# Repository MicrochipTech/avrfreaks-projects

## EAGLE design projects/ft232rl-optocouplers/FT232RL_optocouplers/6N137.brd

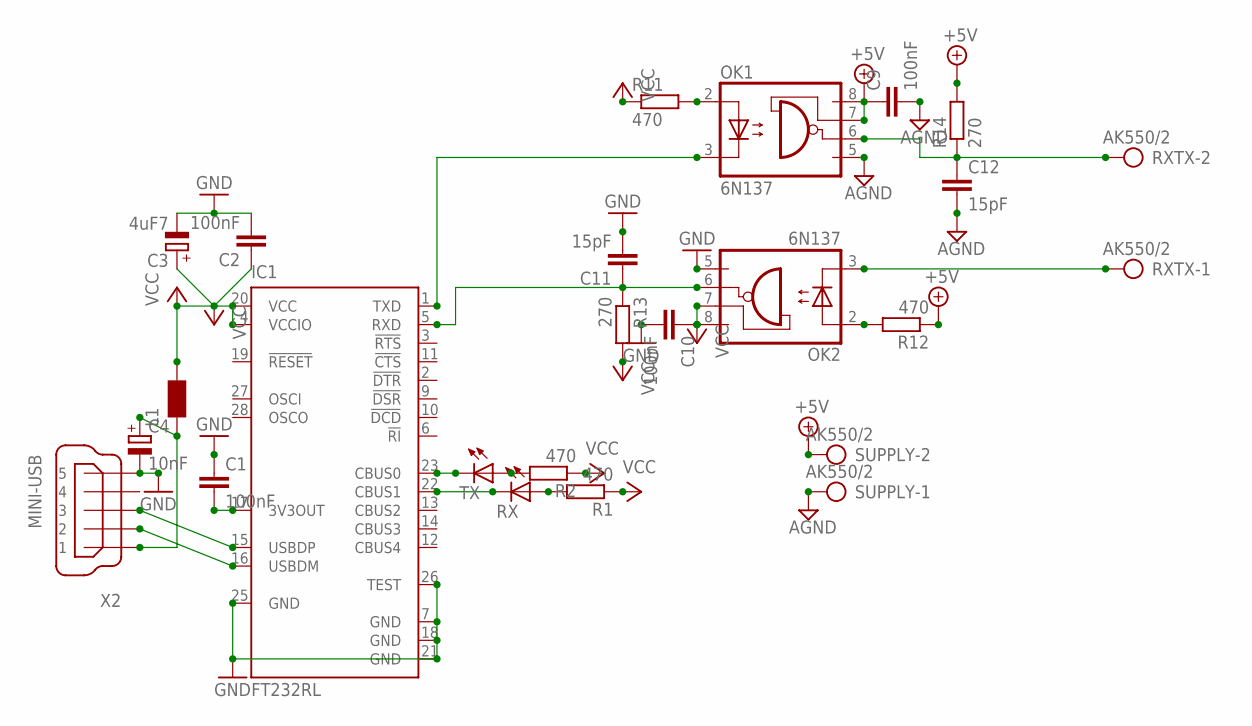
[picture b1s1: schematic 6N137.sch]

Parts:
C1, C2: 100nF; C1206K
C3: 4uF7; 153CLV-0605
C4: 10nF; 153CLV-0405
C9, C10: 100nF; C1206
C11, C12: 15pF; C1206
IC1: FT232RL; SSOP28
L1: WE-CBF_1206; 1206
OK1, OK2: 6N137; DIL08
R1, R2: 470; M1206
R11, R12: 470; R1206
R13, R14: 270; R1206
RX: LEDCHIPLED_1206; CHIPLED_1206
RXTX: AK550/2
SUPPLY: AK550/2
TX: LEDCHIPLED_1206; CHIPLED_1206
X2: MINI-USB; UX60A-MB-5ST

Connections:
+5V: C9.1, OK1.7 (VE), OK1.8 (VCC), R12.1, R14.2, SUPPLY.2
AGND: C9.2, C12.2, OK1.5 (GND), SUPPLY.1
FT_RXD1: C12.1, OK1.6 (VO), R14.1, RXTX.2
FT_TXD1: OK2.3 (C), RXTX.1
GND: C1.1, C2.2, C3.-, C4.-, C10.2, C11.2, IC1.7 (GND), IC1.18 (GND), IC1.21 (GND), IC1.25 (GND), IC1.26 (TEST), OK2.5 (GND), X2.5
unnamed: IC1.16 (USBDM), X2.2
unnamed: IC1.15 (USBDP), X2.3
unnamed: R2.2, TX.A
unnamed: C1.2, IC1.17 (3V3OUT)
unnamed: R1.2, RX.A
unnamed: IC1.23 (CBUS0), TX.C
unnamed: IC1.22 (CBUS1), RX.C
unnamed: OK1.2 (A), R11.2
unnamed: OK2.2 (A), R12.2
RXD1: C11.1, IC1.5 (RXD), OK2.6 (VO), R13.1
TXD1: IC1.1 (TXD), OK1.3 (C)
VBUS: C4.+, L1.1, X2.1
VCC: C2.1, C3.+, C10.1, IC1.4 (VCCIO), IC1.20 (VCC), L1.2, OK2.7 (VE), OK2.8 (VCC), R1.1, R2.1, R11.1, R13.2

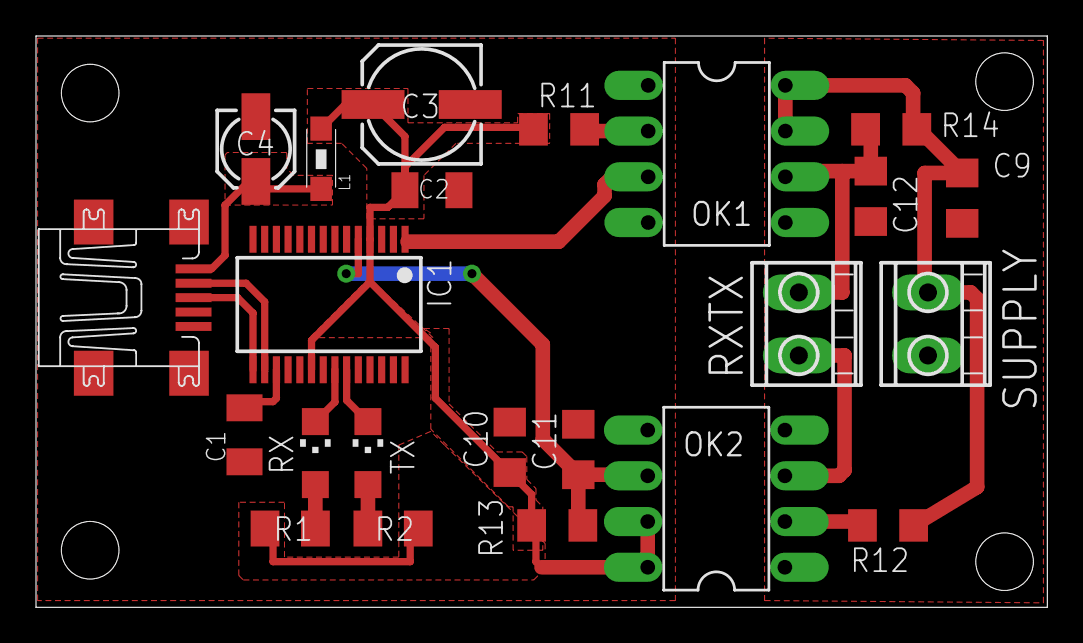
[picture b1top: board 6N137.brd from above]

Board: 2 copper layers, 56.2 x 31.7 mm, 23 parts (0 on the bottom side), 18 nets.

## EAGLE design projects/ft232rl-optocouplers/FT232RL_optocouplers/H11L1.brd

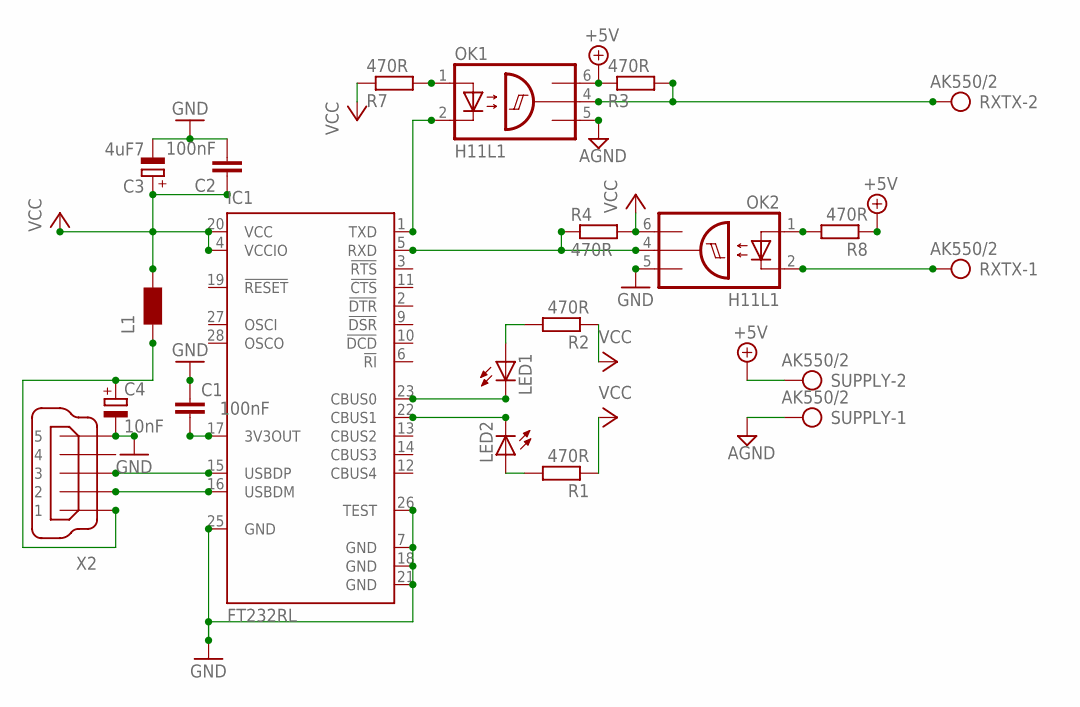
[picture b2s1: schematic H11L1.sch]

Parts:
C1, C2: 100nF; C1206K
C3: 4uF7; 140CLH-0810
C4: 10nF; 153CLV-0405
IC1: FT232RL; SSOP28
L1: WE-CBF_1206; 1206
LED1, LED2: LEDCHIPLED_1206; CHIPLED_1206
OK1, OK2: H11L1; DIL06
R1, R2, R3, R4, R7, R8: 470R; M1206
RXTX: AK550/2
SUPPLY: AK550/2
X2: MINI-USB-SHIELD-UX60A-MB-5ST; UX60A-MB-5ST

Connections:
+5V: OK1.6 (VCC), R3.1, R8.1, SUPPLY.2
AGND: OK1.5 (GND), SUPPLY.1
GND: C1.1, C2.2, C3.-, C4.-, IC1.7 (GND), IC1.18 (GND), IC1.21 (GND), IC1.25 (GND), IC1.26 (TEST), OK2.5 (GND), X2.5
unnamed: IC1.16 (USBDM), X2.2
unnamed: IC1.15 (USBDP), X2.3
unnamed: LED1.A, R2.2
unnamed: C1.2, IC1.17 (3V3OUT)
unnamed: LED2.A, R1.2
unnamed: IC1.23 (CBUS0), LED1.C
unnamed: IC1.22 (CBUS1), LED2.C
unnamed: C4.+, L1.1, X2.1
unnamed: OK1.4 (OUT), R3.2, RXTX.2
unnamed: IC1.5 (RXD), OK2.4 (OUT), R4.1
unnamed: OK1.1 (A), R7.2
unnamed: OK2.1 (A), R8.2
unnamed: OK2.2 (C), RXTX.1
unnamed: IC1.1 (TXD), OK1.2 (C)
VCC: C2.1, C3.+, IC1.4 (VCCIO), IC1.20 (VCC), L1.2, OK2.6 (VCC), R1.1, R2.1, R4.2, R7.1

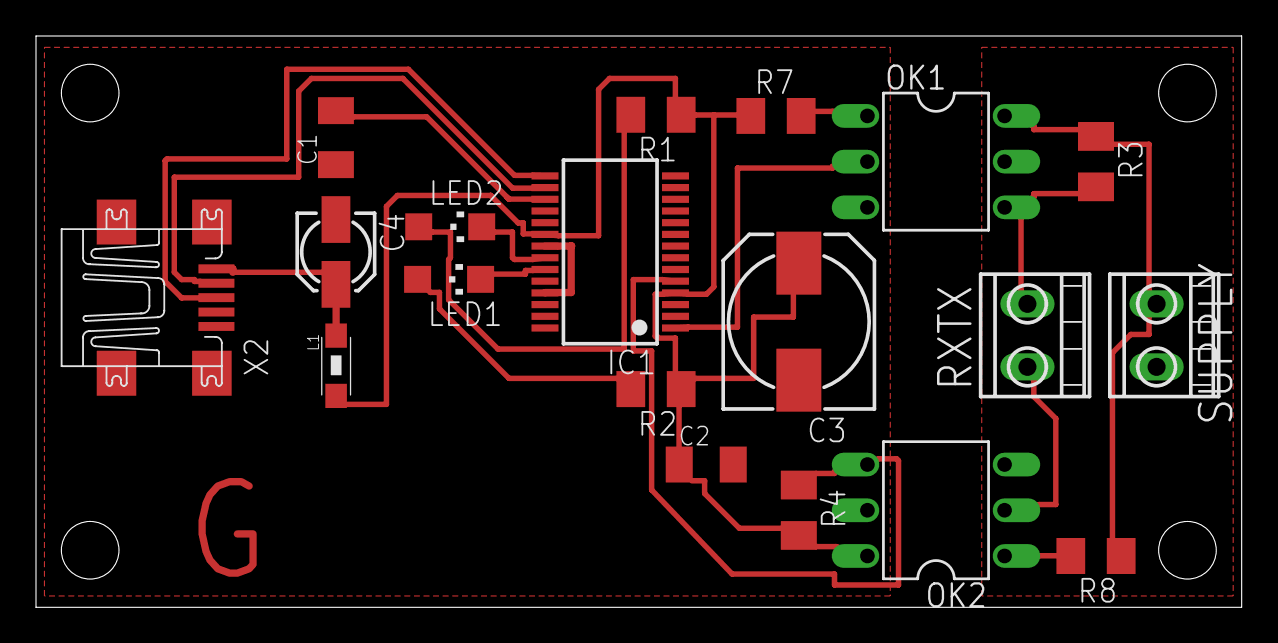
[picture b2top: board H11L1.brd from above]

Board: 2 copper layers, 67.0 x 31.7 mm, 19 parts (0 on the bottom side), 18 nets.

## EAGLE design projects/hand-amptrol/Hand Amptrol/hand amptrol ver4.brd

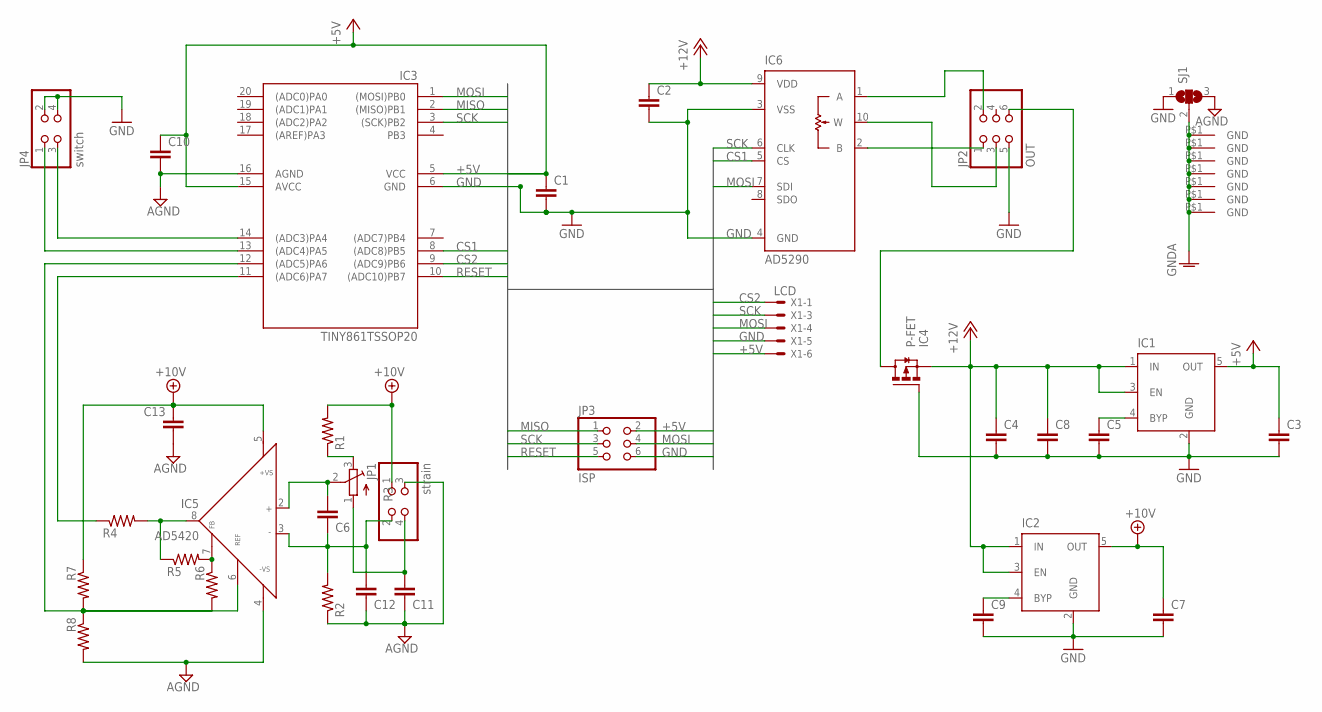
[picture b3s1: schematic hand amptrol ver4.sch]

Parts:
C1, C2, C3, C5, C6, C7, C8, C9, C10, C11, C12, C13: C-EUC0603; C0603
C4: C-EUC1206; C1206
IC1, IC2: MIC5219XX; SOT23-5
IC3: TINY861TSSOP20; TSSOP20
IC4: P-FET; SOT23
IC5: AD5420; MSOP08
IC6: AD5290; MSOP10
JP1: strain; 2X02
JP2: OUT; 2X03
JP3: ISP; 2X03
JP4: switch; 2X02
R1, R2, R4, R5, R6, R7, R8: R-US_R0603; R0603
R3: TRIM_EU-3223W; 3223W
SJ1: SJ2W; SJ_2
U$5, U$6, U$7, U$8, U$9, U$10, U$11: GRDSMALL; GNDSMALL
X1: LCD; 22-23-2061

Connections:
+5V: C1.1, C3.1, C10.1, IC1.5 (OUT), IC3.5 (VCC), IC3.15 (AVCC), JP3.2, X1.6
+10V: C7.1, C13.1, IC2.5 (OUT), IC5.5 (+VS), JP1.1, R1.2, R7.1
+12V: C2.1, C4.1, C8.1, IC1.1 (IN), IC1.3 (EN), IC2.1 (IN), IC2.3 (EN), IC4.2 (S), IC6.9 (VDD)
+12VIN: IC4.3 (D), JP2.6
AGND: C10.2, C11.1, C12.1, C13.2, IC3.16 (AGND), IC5.4 (-VS), JP1.3, R2.1, R8.2, SJ1.3
CS1: IC3.8 ((ADC8)PB5), IC6.5 (CS)
CS2: IC3.9 ((ADC9)PB6), X1.1
GND: C1.2, C2.2, C3.2, C4.2, C5.2, C7.2, C8.2, C9.2, IC1.2 (GND), IC2.2 (GND), IC3.6 (GND), IC4.1 (G), IC6.3 (VSS), IC6.4 (GND), JP2.5, JP3.6, JP4.2, JP4.4, SJ1.1, X1.5
GNDA: SJ1.2, U$5.P$1, U$6.P$1, U$7.P$1, U$8.P$1, U$9.P$1, U$10.P$1, U$11.P$1
MISO: IC3.2 ((MISO)PB1), JP3.1
MOSI: IC3.1 ((MOSI)PB0), IC6.7 (SDI), JP3.4, X1.4
unnamed: R1.1, R3.3 (E)
unnamed: IC3.11 ((ADC6)PA7), R4.1
unnamed: IC6.2 (B), JP2.1
unnamed: C5.1, IC1.4 (BYP)
unnamed: C9.1, IC2.4 (BYP)
unnamed: IC3.13 ((ADC4)PA5), JP4.1
unnamed: IC6.1 (A), JP2.2
unnamed: IC6.10 (W), JP2.3
unnamed: C6.2, IC5.2 (IN+), R3.2 (S)
unnamed: IC3.14 ((ADC3)PA4), JP4.3
unnamed: IC5.8 (OUT), R4.2, R5.1
unnamed: IC5.7 (FB), R5.2, R6.1
unnamed: IC3.12 ((ADC5)PA6), IC5.6 (REF), R6.2, R7.2, R8.1
RESET: IC3.10 ((ADC10)PB7), JP3.5
SCK: IC3.3 ((SCK)PB2), IC6.6 (CLK), JP3.3, X1.3
STRAIN+: C6.1, C12.2, IC5.3 (IN-), JP1.2, R2.2
STRAIN-: C11.2, JP1.4, R3.1 (A)

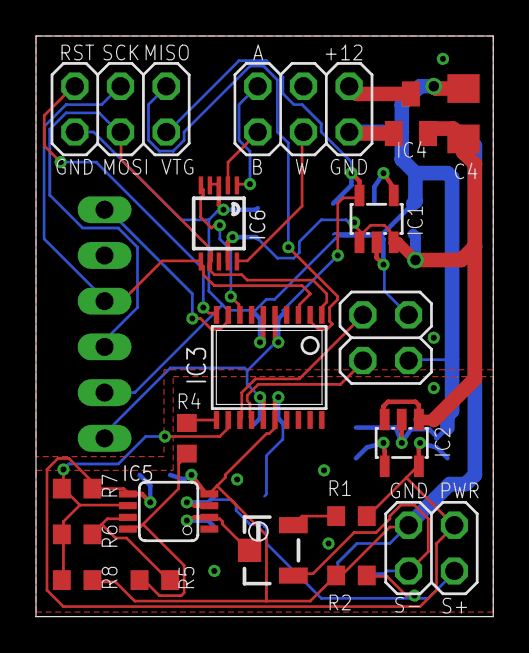
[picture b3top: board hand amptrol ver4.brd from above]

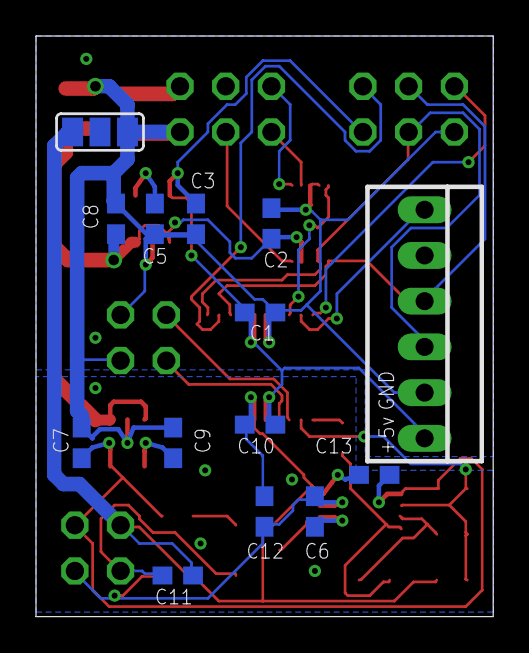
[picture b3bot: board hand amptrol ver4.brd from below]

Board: 2 copper layers, 25.4 x 32.3 mm, 40 parts (14 on the bottom side), 28 nets.
